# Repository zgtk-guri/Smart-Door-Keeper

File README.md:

### トランジスタ技術 IoT製作コーナー
## NFCカードリーダ×Wi-Fi/Bluetoothマイコンで作るIoT電子錠
# 「Smart Door Keeper」ダウンロードページ

## 2018年9月号 前編 NFCの仕組みとハードウェア製作
* [3Dプリントファイル](3DPrint/README.md)
* [回路図・基板パターン](Circuit/README.md)

## 2018年10月号 後編
* [ESP32のプログラム(Platform IO, Arduino Core使用)](https://github.com/zgtk-guri/Smart-Door-Keeper-ESP32/tree/toragi1810)
* [Androidアプリのプログラム](https://github.com/zgtk-guri/Smart-Door-Keeper-Android/tree/toragi1810)

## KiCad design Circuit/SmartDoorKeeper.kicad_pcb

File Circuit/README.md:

# Smart Door Keeper 回路図・基板パターンファイル

* [SmartDoorKeeper.pro](SmartDoorKeeper.pro) KiCad 4.0.7 プロジェクトファイル
* [SmartDoorKeeper.sch](SmartDoorKeeper.sch) Eeschema 回路図ファイル
* [SmartDoorKeeper-schematic.pdf](SmartDoorKeeper-schematic.pdf) 回路図PDFファイル
* [SmartDoorKeeper.kicad_pcb](SmartDoorKeeper.kicad_pcb) Pcbnew 基板パターンファイル

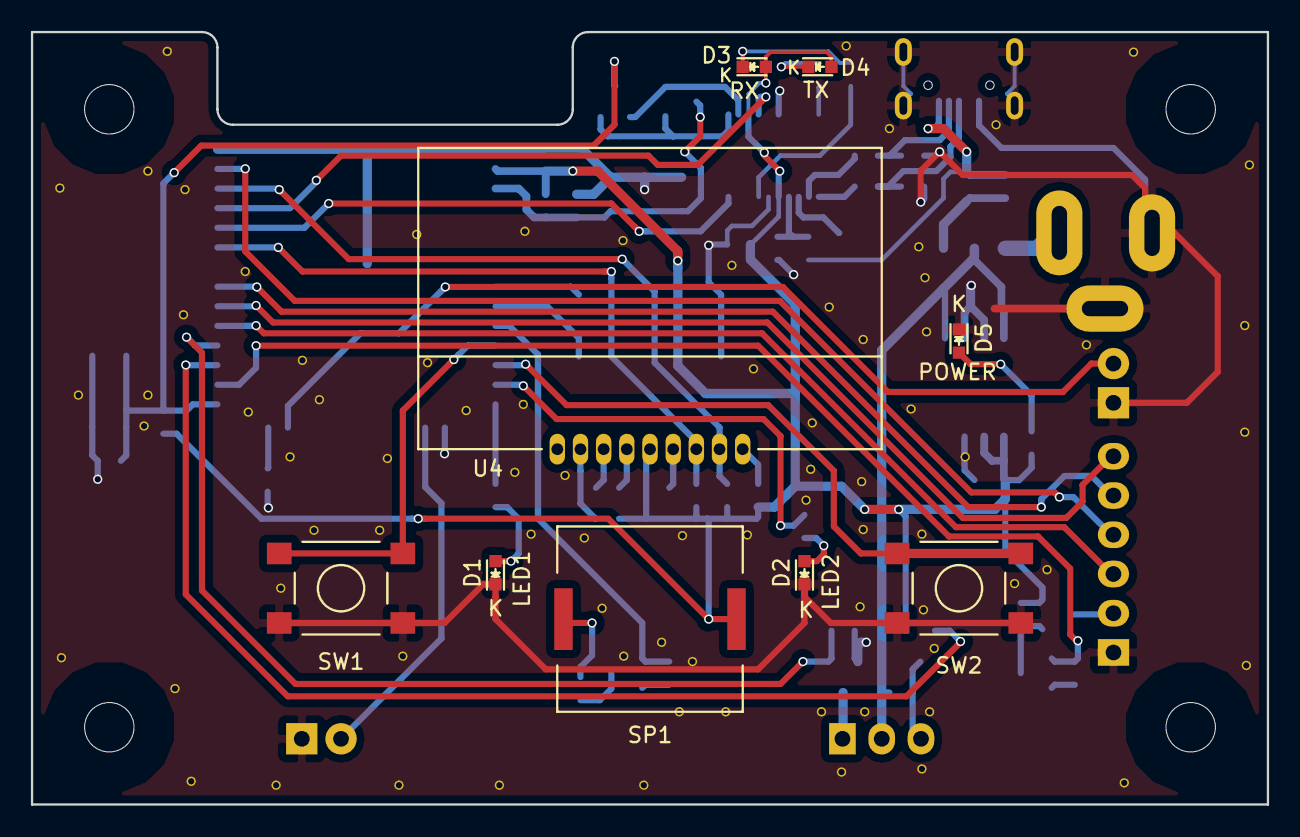
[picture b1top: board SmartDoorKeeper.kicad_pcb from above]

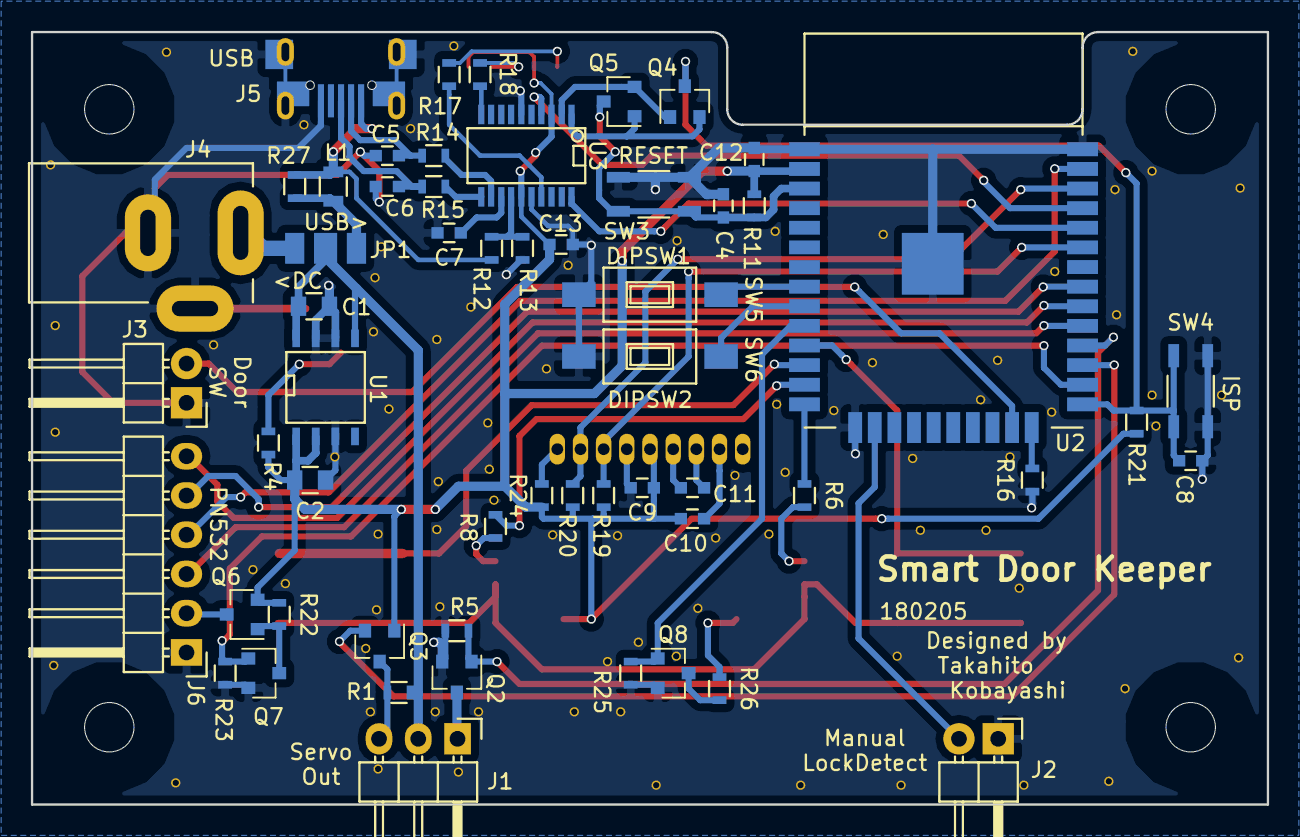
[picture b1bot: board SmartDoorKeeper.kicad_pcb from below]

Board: 2 copper layers, 80.0 x 50.0 mm, 65 parts (56 on the bottom side), 54 nets.

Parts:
C1, C2: 10u; C_0805
C4, C8: 1000p; C_0603
C5, C6: 47p; C_0603
C7, C9, C12, C13: 0.1u; C_0603
C10, C11: 1u; C_0603
D1: LED1(Red); LED_0603
D2: LED2(Red); LED_0603
D3: RX(Blue); LED_0603
D4: TX(White); LED_0603
D5: Power(Red); LED_0603
J1: ServoOut; Pin_Header_Angled_1x03
J2: LockDetect; Pin_Header_Angled_1x02
J3: DoorSwitch; Pin_Header_Angled_1x02
J4: +5V DC Input; MJ-179PH
J5: USB_OTG; MicroUSB_YANXINLIANG_and_ZX62-B-5PA
J6: PN532_SPI; Pin_Header_Angled_1x06
JP1: Power Source Select; SMD-Jumper-3
L1: MI0805K400R-10; R_0805
Q2, Q3, Q4, Q5, Q7, Q8: IRLML6344TRPbF; SOT-23
Q6: IRLML6402; SOT-23
R1, R5, R11, R13, R16, R19, R20, R22, R23, R24, R25: 10k; R_0603
R4, R6, R8, R17, R18, R26: 1k; R_0603
R12, R21: 4.7k; R_0603
R14, R15: 27; R_0603
R27: 0; R_0603
SP1: SPEAKER; PKLCS1212E4001-R1
SW1: SW1; 6mm_tactil_switch_SMD
SW2: SW2; 6mm_tactil_switch_SMD
SW3: RESET; SKRPACE010
SW4: ISP; SKRPACE010
SW5, SW6: SPST; SW_SPST_FSMSM
U1: LT1963A; SOIC-8-N
U2: ESP-WROOM-32
U3: FT231XS; SSOP-20
U4: AQM0802A

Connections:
+3V3: C2.1, C9.1, C10.1, C12.1, C13.1, D3.2, D4.2, Q3.1, Q6.2, R4.1, R11.1, R19.1, R20.1, R21.1, R22.1, R24.1, SP1.1, U1.1, U1.2, U2.2, U3.3, U3.15, U4.5
+5V: C1.1, J1.2, JP1.2, R1.1, U1.5, U1.8
Buzzer: Q8.1, R25.2, U2.10
DIPSW1: SW5.1, U2.8
DIPSW2: SW6.1, U2.9
DoorSW: J3.2, U2.23
EN: C4.1, Q5.3, R11.2, SW3.1, U2.3
GND: C1.2, C2.2, C4.2, C5.2, C6.2, C7.2, C8.2, C9.2, C12.2, C13.2, D1.1, D2.1, D5.1, J2.1, J3.1, J4.2, J4.3, J5.5, J5.6, J6.1, Q2.2, Q7.2, Q8.2, R5.2, R13.2, R16.2, R23.2, R25.1, SW1.2, SW2.2, SW3.2, SW4.2, SW5.2, SW6.2, U1.3, U1.6, U1.7, U2.1, U2.15, U2.38, U2.39, U3.6, U3.16, U4.6
IO0: C8.1, Q4.3, R21.2, SW4.1, U2.25
LED1: R6.1, U2.14
LED2: R8.1, U2.13
MISO: J6.5, U2.31
MOSI: J6.4, U2.37
ManualLockDetect: J2.2, U2.16
unnamed: C5.1, J5.2, R14.2
unnamed: C6.1, J5.3, R15.2
unnamed: C7.1, U3.13
unnamed: C10.2, U4.2
unnamed: C11.1, U4.3
unnamed: C11.2, U4.4
unnamed: D1.2, R6.2
unnamed: D2.2, R8.2
unnamed: D3.1, R17.1
unnamed: D4.1, R18.1
unnamed: D5.2, R4.2
unnamed: J1.1, Q2.3
unnamed: J1.3, Q3.3, R1.2
unnamed: J4.1, JP1.1
unnamed: J5.1, L1.2, R12.1, R27.1
unnamed: J6.2, Q6.3
unnamed: JP1.3, L1.1, R27.2
unnamed: Q4.1, Q5.2, U3.2
unnamed: Q4.2, Q5.1, U3.1
unnamed: Q6.1, Q7.3, R22.2
unnamed: Q8.3, R26.2
unnamed: R12.2, R13.1, U3.14
unnamed: R14.1, U3.12
unnamed: R15.1, U3.11
unnamed: R16.1, U2.24
unnamed: R17.2, U3.17
unnamed: R18.2, U3.10
unnamed: R24.2, U4.9
unnamed: R26.1, SP1.2
unnamed: U2.34, U3.20
unnamed: U2.35, U3.4
PN532Power: Q7.1, R23.1, U2.26
SCK: J6.6, U2.30
SCL: R20.2, U2.36, U4.8
SDA: R19.2, U2.33, U4.7
SS: J6.3, U2.29
SW1: SW1.1, U2.11
SW2: SW2.1, U2.12
ServoPower: Q2.1, R5.1, U2.28
ServoSignal: Q3.2, U2.27

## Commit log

2018-07-12 リポジトリを作成
2018-07-12 3Dプリントのファイルを追加
2018-07-12 3Dプリントファイルの一覧を作成
2018-07-12 画像を追加
2018-07-12 3Dプリントファイル一覧にリンクを追加
2018-07-12 READMEに3Dプリントファイルの一覧へのリンクを追加
2018-07-13 ExcelとPowerPointのファイルを追加
2018-07-13 KiCadの設計ファイルを追加
2018-07-13 KiCadのファイルに関するReadmeを追加
2018-08-08 Smart Door Keyper -> Smart Door Keeperに変更
2018-09-05 ESP32のプログラムへのリンクを追加
2018-09-05 Submoduleとして，ESP32のプログラムを追加
2018-09-11 Androidアプリを追加
